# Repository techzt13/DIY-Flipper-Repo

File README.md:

# DIY Flipper Zero (STM32WB55 "FCFZ-style" clone)

My **Hack Club Fallen** project: a hand-built Flipper Zero clone based on the
**WeAct STM32WB55CGU6** board, running the official Flipper / Momentum firmware
(via the open-source FCFZ / Nucleus Dark / Flipper-Diy community port).
Remote participant — Hong Kong 🇭🇰

## What it does
- **Sub-GHz (433 MHz, CC1101)** — read/save/replay remotes (HK band, not 315)
- **NFC (ST25R3916)** — the real Flipper NFC chip, full read/emulate
- **Infrared** — receive + transmit remotes (TV-b-gone style)
- **iButton / 1-Wire**, **BadUSB (USB-C)**, **GPIO/UART** breakout
- **SD card** for saved captures, ST7565 monochrome LCD, 6-button nav
- 18650 battery → TP4056 charge → MT3608 boost → 5 V rail

Known clone limitations (firmware/secure-enclave, not fixable in hardware):
U2F and KeeLoq need factory keys; 125 kHz RFID is not supported by the
FCFZ firmware build; no speaker/vibration.

## Screenshots

### PCB (routed, 2-layer)

### Full 3D assembly (3D-printed case)

### Wiring diagram

## Repo contents
| Path | What |
|---|---|
| `bom.csv` | Fallen funding BOM (links, min quantities, justifications) |
| `kicad/diy-flipper.kicad_pro/.kicad_sch/.kicad_pcb/.kicad_prl` | Full KiCad 8 project — carrier PCB the WeAct board + modules plug into |
| `kicad/gerbers/` | Gerber + drill files for fab (HASL, cheapest option) |
| `case/bottom_shell.stl`, `case/lid.stl` | 3D-printable 2-part case (ready to slice) |
| `case/case_step.py` | CadQuery source → exports STEP (run in Google Colab) |
| `case/*.step` | STEP exports of the case |

## Build
1. **PCB**: send `kicad/gerbers/` to the cheapest fab (HASL, 1.6 mm, any colour).
2. **Modules**: plug in per the schematic — WeAct board (J1/J2 headers),
   ST7565 LCD (J3), CC1101 433 MHz (J4), micro-SD module (J5),
   ST25R3916 NFC (J6), IR RX (J7), iButton (J8), UART debug (J9), 5 V in (J10).
3. **Buttons**: 6× tactile through SN74HC165 shift register (U1) with 10 kΩ
   pull-downs; inputs H=LEFT G=UP F=OK E=RIGHT D=DOWN C=BACK, SH/LD=PH3.
4. **IR TX**: PB9 → 1 kΩ → 2N3904 base; collector → IR LED → 47 Ω → 3V3.
5. **Power**: 18650 → TP4056 → MT3608 (set to 5.0 V!) → slide switch → 5 V pin.
   The MT3608 is required — the onboard regulator sags on a low battery.
6. **Firmware**: STM32CubeProgrammer (hold BOOT0) → write OTP at 0x1FFF7000 →
   qFlipper "Install from file" → flash the FCFZ-modified Momentum `.dfu`
   (Zadig for the USB driver on Windows). Verify the pinout in the exact `.dfu`
   you flash matches the schematic before powering anything on!

## Pin map (matches prebuilt FCFZ/Momentum .dfu)
SPI bus: SCK=PB3, MISO=PB4, MOSI=PB5 · LCD: CS=PB2, DC=PB1, RST=PB0 ·
SD: CS=PA4 · CC1101: CSN=PA7, GDO0=PA1 · NFC: CS=PE4, IRQ=PA2 ·
IR RX=PA0, TX=PB9 · iButton=PB8 · UART: TX=PB6, RX=PB7

## Build log
- [x] Research + verified parts list (Amazon HK, ST official NFC board)
- [x] Wiring schematic + pinout cross-checked vs community sources & videos
- [x] KiCad schematic + PCB (carrier board, 130×105 mm)
- [x] Case CAD (STL + STEP)
- [ ] Order parts on the HCB grant card
- [ ] Assemble + flash firmware
- [ ] Demo video → Build Submission 🍂

## Credits
Firmware port & reference pinout: FCFZ / Nucleus Dark / Flipper-Diy community,
Momentum firmware, flipperdevices.

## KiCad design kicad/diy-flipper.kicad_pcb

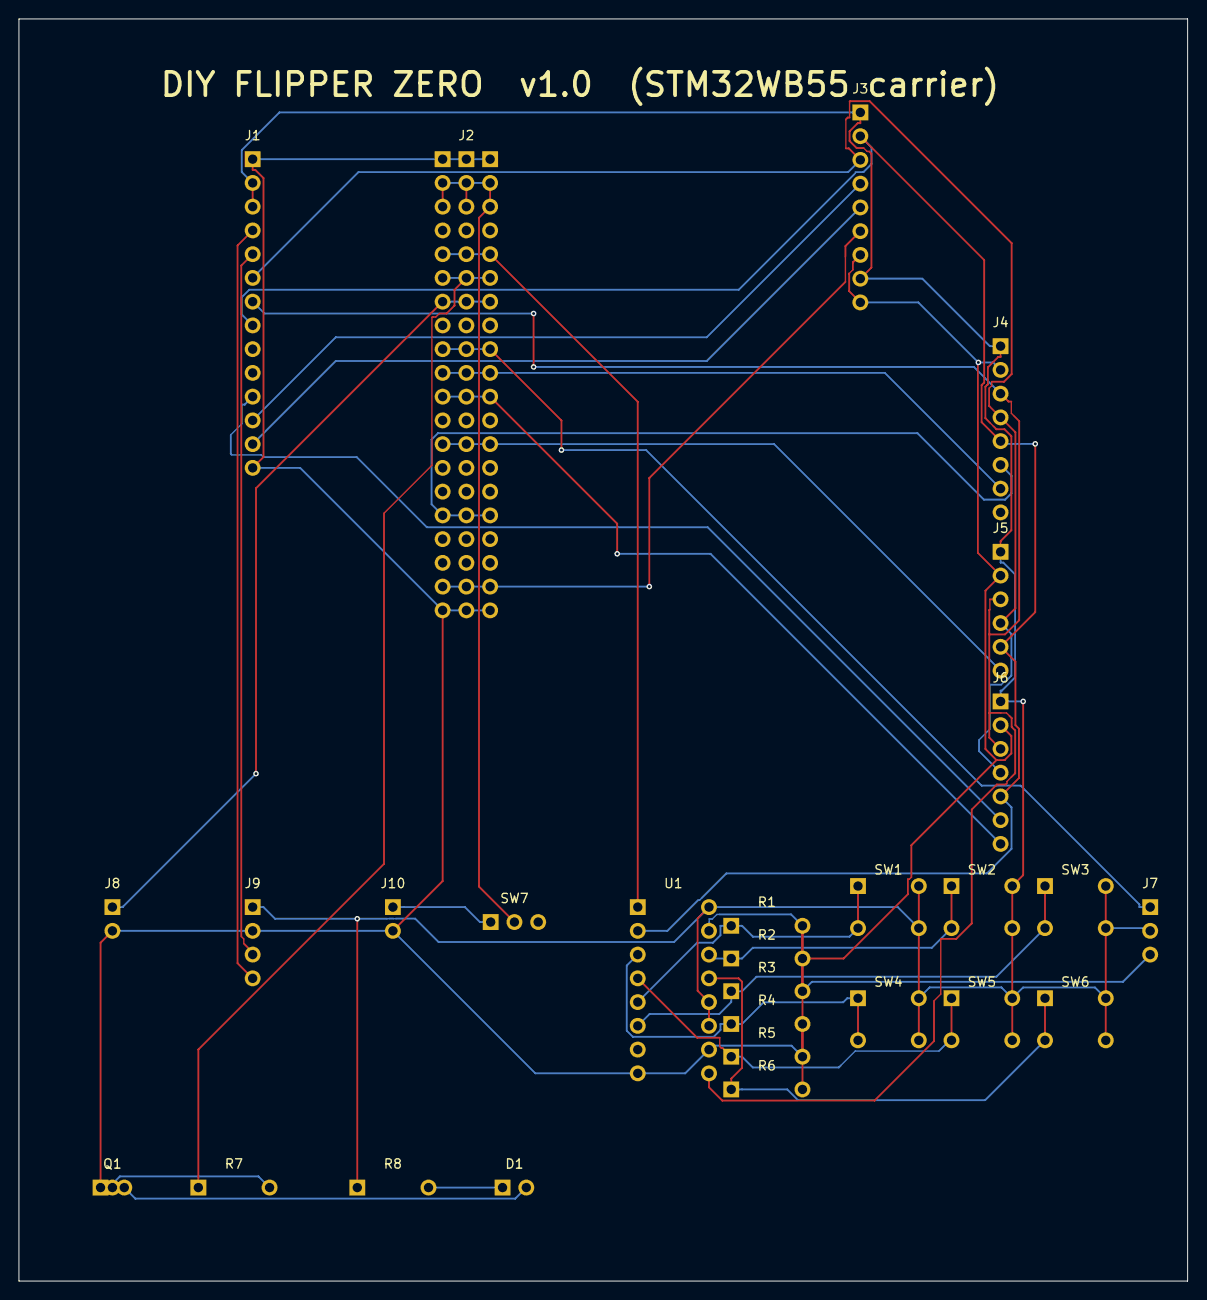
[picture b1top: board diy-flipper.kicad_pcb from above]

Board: 2 copper layers, 125.0 x 135.0 mm, 28 parts (0 on the bottom side), 30 nets.

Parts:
D1: IR_LED; LED_D5.0mm
J1: MCU top; PinHeader_1x14_P2.54mm_Vertical
J2: MCU bottom (0.8/0.9/1.0in rows); PinHeader_1x20_P2.54mm_Vertical_3row
J3: ST7565 LCD; PinHeader_1x09_P2.54mm_Vertical
J4: CC1101; PinHeader_1x08_P2.54mm_Vertical
J5: MicroSD; PinHeader_1x06_P2.54mm_Vertical
J6: NFC; PinHeader_1x07_P2.54mm_Vertical
J7: IR-RX; PinHeader_1x03_P2.54mm_Vertical
J8: iButton; PinHeader_1x02_P2.54mm_Vertical
J9: UART; PinHeader_1x04_P2.54mm_Vertical
J10: PWR; PinHeader_1x02_P2.54mm_Vertical
Q1: 2N3904; TO-92_Inline
R1, R2, R3, R4, R5, R6: 10k; R_Axial_DIN0207_P7.62mm
R7: 1k; R_Axial_DIN0207_P7.62mm
R8: 47R; R_Axial_DIN0207_P7.62mm
SW1, SW2, SW3, SW4, SW5, SW6: SW_Push; SW_PUSH_6mm
SW7: SW_SPDT
U1: SN74HC165N; DIP-16_W7.62mm

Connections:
+3V3: J1.2, J1.3, J3.1, J3.8, J4.1, J5.1, J6.1, J7.2, J9.1, R8.1, SW1.2, SW2.2, SW3.2, SW4.2, SW5.2, SW6.2, U1.11, U1.12, U1.16
+5V: J2.2, J2.2a, J2.2b, J2.3, J2.3a, J2.3b, SW7.2
+5V_SW: J10.1, SW7.1
BTN_BACK: R6.1, SW6.1, U1.13
BTN_DOWN: R2.1, SW2.1, U1.14
BTN_LATCH: J2.5, J2.5a, J2.5b, U1.1
BTN_LEFT: R3.1, SW3.1, U1.6
BTN_OK: R5.1, SW5.1, U1.4
BTN_RIGHT: R4.1, SW4.1, U1.3
BTN_UP: R1.1, SW1.1, U1.5
CC_CSN: J2.16, J2.16a, J2.16b, J4.6
CC_GDO0: J2.10, J2.10a, J2.10b, J4.7
GND: J1.1, J1.14, J2.1, J2.1a, J2.1b, J2.20, J2.20a, J2.20b, J3.7, J3.9, J4.2, J5.2, J6.2, J7.3, J8.2, J9.2, J10.2, Q1.1, R1.2, R2.2, R3.2, R4.2, R5.2, R6.2, U1.8, U1.10, U1.15
IBTN_DATA: J2.7, J2.7a, J2.7b, J8.1
IR_RX: J2.9, J2.9a, J2.9b, J7.1
IR_TX: J2.6, J2.6a, J2.6b, R7.1
IR_TX_A: D1.1, R8.2
IR_TX_B: Q1.2, R7.2
IR_TX_C: D1.2, Q1.3
LCD_CS: J2.19, J2.19a, J2.19b, J3.6
LCD_DC: J1.12, J3.4
LCD_RST: J1.13, J3.5
NFC_CS: J1.11, J6.6
NFC_IRQ: J2.11, J2.11a, J2.11b, J6.7
SD_CS: J2.13, J2.13a, J2.13b, J5.6
SPI_MISO: J1.7, J4.3, J5.3, J6.3, U1.9
SPI_MOSI: J1.6, J3.3, J4.4, J5.4, J6.4
SPI_SCK: J1.8, J3.2, J4.5, J5.5, J6.5, U1.2
UART_RX: J1.4, J9.4
UART_TX: J1.5, J9.3
